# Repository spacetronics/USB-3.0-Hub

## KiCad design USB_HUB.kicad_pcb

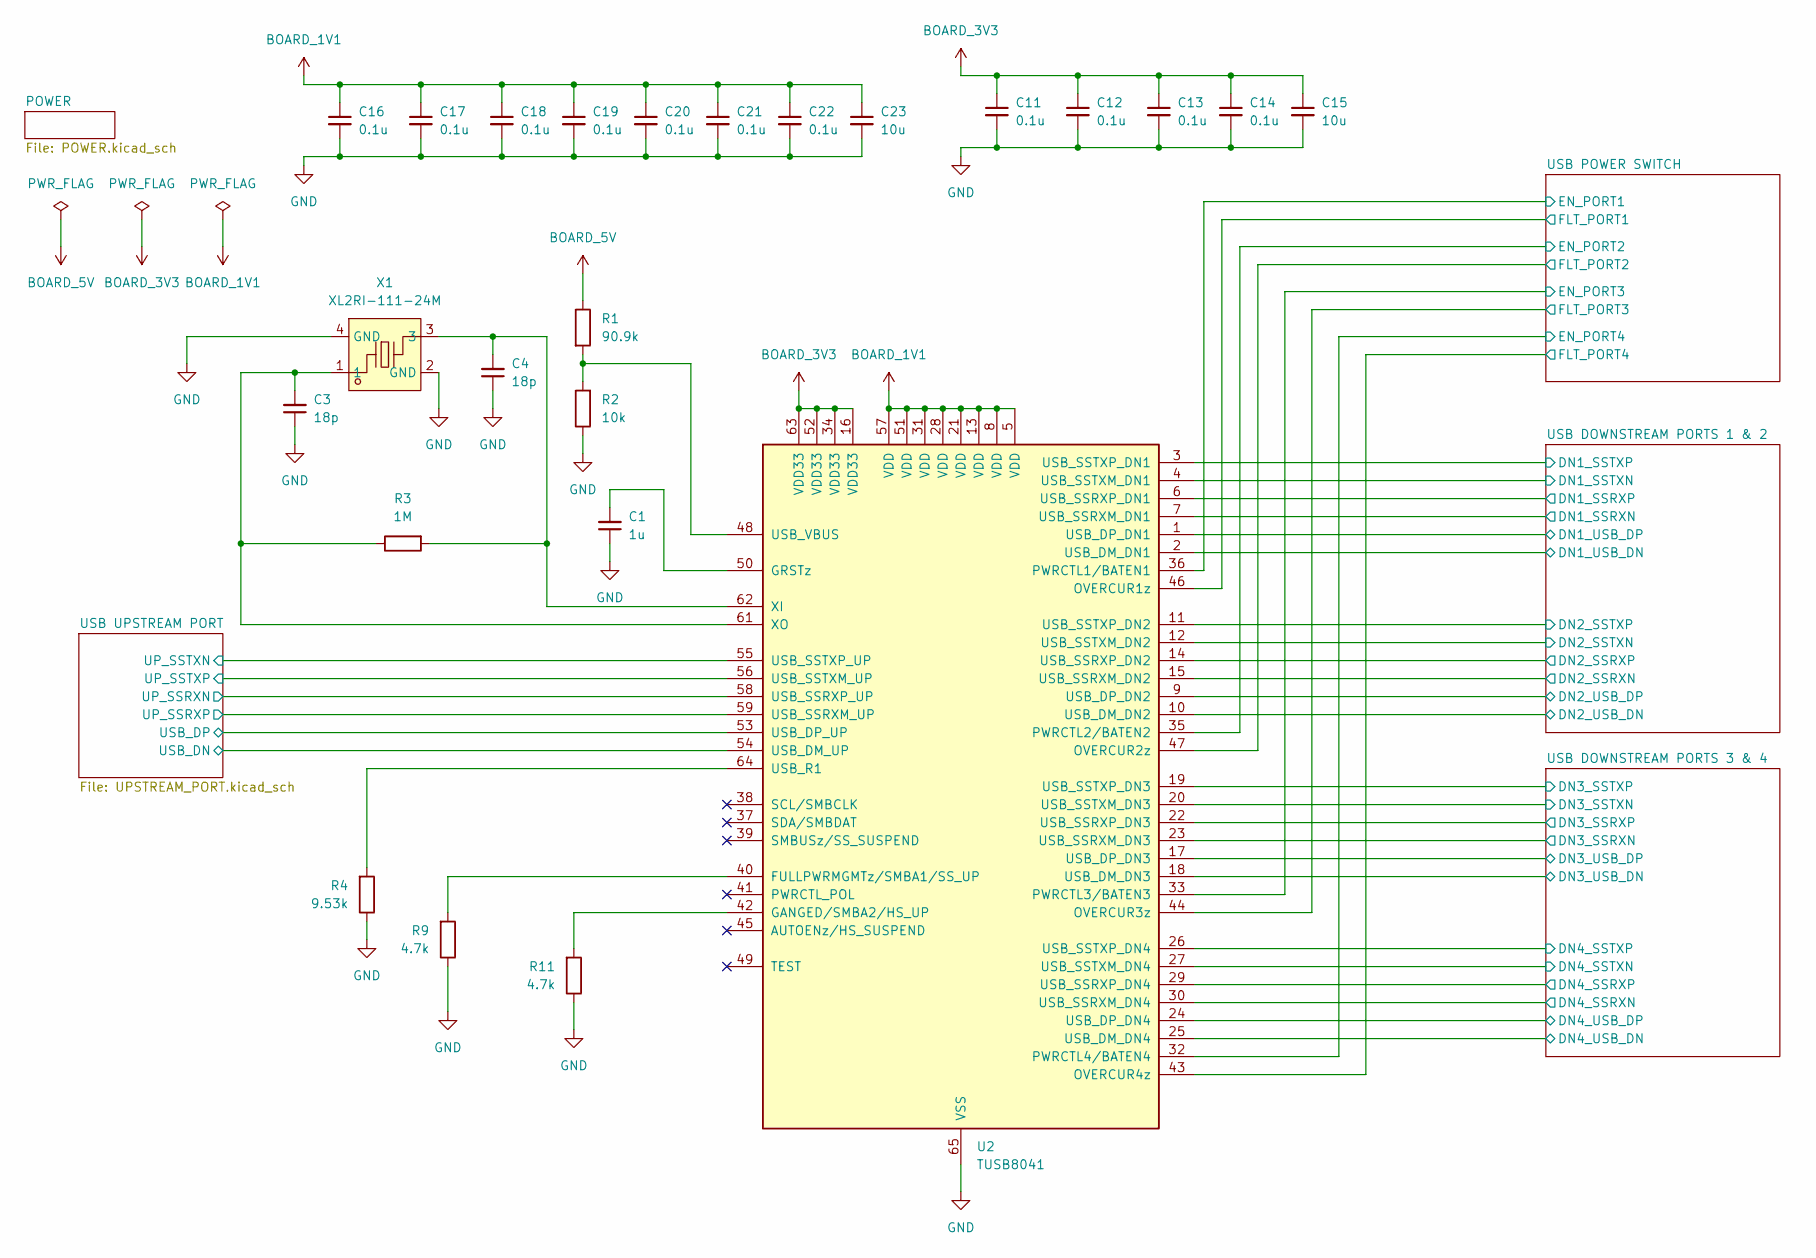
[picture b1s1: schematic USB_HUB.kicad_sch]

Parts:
C1: 1u; C_0402_1005Metric
C3, C4: 18p; C_0402_1005Metric
C11, C12, C13, C14, C16, C17, C18, C19, C20, C21, C22: 0.1u; C_0402_1005Metric
C15, C23: 10u; C_0402_1005Metric
R1: 90.9k; R_0402_1005Metric
R2: 10k; R_0402_1005Metric
R3: 1M; R_0402_1005Metric
R4: 9.53k; R_0402_1005Metric
R9, R11: 4.7k; R_0402_1005Metric
U2: TUSB8041; QFN-64-1EP_9x9mm_P0.5mm_EP6x6mm_ThermalVias
X1: XL2RI-111-24M; CRYSTAL-SMD_4P-L3.2-W2.5-BL; MPN XL2RI-111-24M; LCSC Part C20617586

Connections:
/USB DOWNSTREAM PORTS 1 & 2/DN1_SSRXN: U2.7 (USB_SSRXM_DN1); also elsewhere on the board
/USB DOWNSTREAM PORTS 1 & 2/DN1_SSRXP: U2.6 (USB_SSRXP_DN1); also elsewhere on the board
/USB DOWNSTREAM PORTS 1 & 2/DN1_SSTXN: U2.4 (USB_SSTXM_DN1); also elsewhere on the board
/USB DOWNSTREAM PORTS 1 & 2/DN1_SSTXP: U2.3 (USB_SSTXP_DN1); also elsewhere on the board
/USB DOWNSTREAM PORTS 1 & 2/DN1_USB_DN: U2.2 (USB_DM_DN1); also elsewhere on the board
/USB DOWNSTREAM PORTS 1 & 2/DN1_USB_DP: U2.1 (USB_DP_DN1); also elsewhere on the board
/USB DOWNSTREAM PORTS 1 & 2/DN2_SSRXN: U2.15 (USB_SSRXM_DN2); also elsewhere on the board
/USB DOWNSTREAM PORTS 1 & 2/DN2_SSRXP: U2.14 (USB_SSRXP_DN2); also elsewhere on the board
/USB DOWNSTREAM PORTS 1 & 2/DN2_SSTXN: U2.12 (USB_SSTXM_DN2); also elsewhere on the board
/USB DOWNSTREAM PORTS 1 & 2/DN2_SSTXP: U2.11 (USB_SSTXP_DN2); also elsewhere on the board
/USB DOWNSTREAM PORTS 1 & 2/DN2_USB_DN: U2.10 (USB_DM_DN2); also elsewhere on the board
/USB DOWNSTREAM PORTS 1 & 2/DN2_USB_DP: U2.9 (USB_DP_DN2); also elsewhere on the board
/USB DOWNSTREAM PORTS 3 & 4/DN3_SSRXN: U2.23 (USB_SSRXM_DN3); also elsewhere on the board
/USB DOWNSTREAM PORTS 3 & 4/DN3_SSRXP: U2.22 (USB_SSRXP_DN3); also elsewhere on the board
/USB DOWNSTREAM PORTS 3 & 4/DN3_SSTXN: U2.20 (USB_SSTXM_DN3); also elsewhere on the board
/USB DOWNSTREAM PORTS 3 & 4/DN3_SSTXP: U2.19 (USB_SSTXP_DN3); also elsewhere on the board
/USB DOWNSTREAM PORTS 3 & 4/DN3_USB_DN: U2.18 (USB_DM_DN3); also elsewhere on the board
/USB DOWNSTREAM PORTS 3 & 4/DN3_USB_DP: U2.17 (USB_DP_DN3); also elsewhere on the board
/USB DOWNSTREAM PORTS 3 & 4/DN4_SSRXN: U2.30 (USB_SSRXM_DN4); also elsewhere on the board
/USB DOWNSTREAM PORTS 3 & 4/DN4_SSRXP: U2.29 (USB_SSRXP_DN4); also elsewhere on the board
/USB DOWNSTREAM PORTS 3 & 4/DN4_SSTXN: U2.27 (USB_SSTXM_DN4); also elsewhere on the board
/USB DOWNSTREAM PORTS 3 & 4/DN4_SSTXP: U2.26 (USB_SSTXP_DN4); also elsewhere on the board
/USB DOWNSTREAM PORTS 3 & 4/DN4_USB_DN: U2.25 (USB_DM_DN4); also elsewhere on the board
/USB DOWNSTREAM PORTS 3 & 4/DN4_USB_DP: U2.24 (USB_DP_DN4); also elsewhere on the board
/USB POWER SWITCH/EN_PORT1: U2.36 (PWRCTL1/BATEN1); also elsewhere on the board
/USB POWER SWITCH/EN_PORT2: U2.35 (PWRCTL2/BATEN2); also elsewhere on the board
/USB POWER SWITCH/EN_PORT3: U2.33 (PWRCTL3/BATEN3); also elsewhere on the board
/USB POWER SWITCH/EN_PORT4: U2.32 (PWRCTL4/BATEN4); also elsewhere on the board
/USB POWER SWITCH/FLT_PORT1: U2.46 (OVERCUR1z); also elsewhere on the board
/USB POWER SWITCH/FLT_PORT2: U2.47 (OVERCUR2z); also elsewhere on the board
/USB POWER SWITCH/FLT_PORT3: U2.44 (OVERCUR3z); also elsewhere on the board
/USB POWER SWITCH/FLT_PORT4: U2.43 (OVERCUR4z); also elsewhere on the board
/USB UPSTREAM PORT/UP_SSRXN: U2.58 (USB_SSRXP_UP); also elsewhere on the board
/USB UPSTREAM PORT/UP_SSRXP: U2.59 (USB_SSRXM_UP); also elsewhere on the board
/USB UPSTREAM PORT/UP_SSTXN: U2.55 (USB_SSTXP_UP); also elsewhere on the board
/USB UPSTREAM PORT/UP_SSTXP: U2.56 (USB_SSTXM_UP); also elsewhere on the board
/USB UPSTREAM PORT/USB_DN: U2.54 (USB_DM_UP); also elsewhere on the board
/USB UPSTREAM PORT/USB_DP: U2.53 (USB_DP_UP); also elsewhere on the board
BOARD_1V1: C16.1, C17.1, C18.1, C19.1, C20.1, C21.1, C22.1, C23.1, U2.5 (VDD), U2.8 (VDD), U2.13 (VDD), U2.21 (VDD), U2.28 (VDD), U2.31 (VDD), U2.51 (VDD), U2.57 (VDD); also elsewhere on the board
BOARD_3V3: C11.1, C12.1, C13.1, C14.1, C15.1, U2.16 (VDD33), U2.34 (VDD33), U2.52 (VDD33), U2.63 (VDD33); also elsewhere on the board
BOARD_5V: R1.1; also elsewhere on the board
GND: C1.1, C3.1, C4.1, C11.2, C12.2, C13.2, C14.2, C15.2, C16.2, C17.2, C18.2, C19.2, C20.2, C21.2, C22.2, C23.2, R2.1, R4.1, R9.1, R11.1, U2.65 (VSS), X1.2 (GND), X1.4 (GND); also elsewhere on the board
unnamed: R9.2, U2.40 (FULLPWRMGMTz/SMBA1/SS_UP)
unnamed: R11.2, U2.42 (GANGED/SMBA2/HS_UP)
unnamed: C1.2, U2.50 (GRSTz)
unnamed: R4.2, U2.64 (USB_R1)
unnamed: R1.2, R2.2, U2.48 (USB_VBUS)
unnamed: C4.2, R3.2, U2.62 (XI), X1.3
unnamed: C3.2, R3.1, U2.61 (XO), X1.1

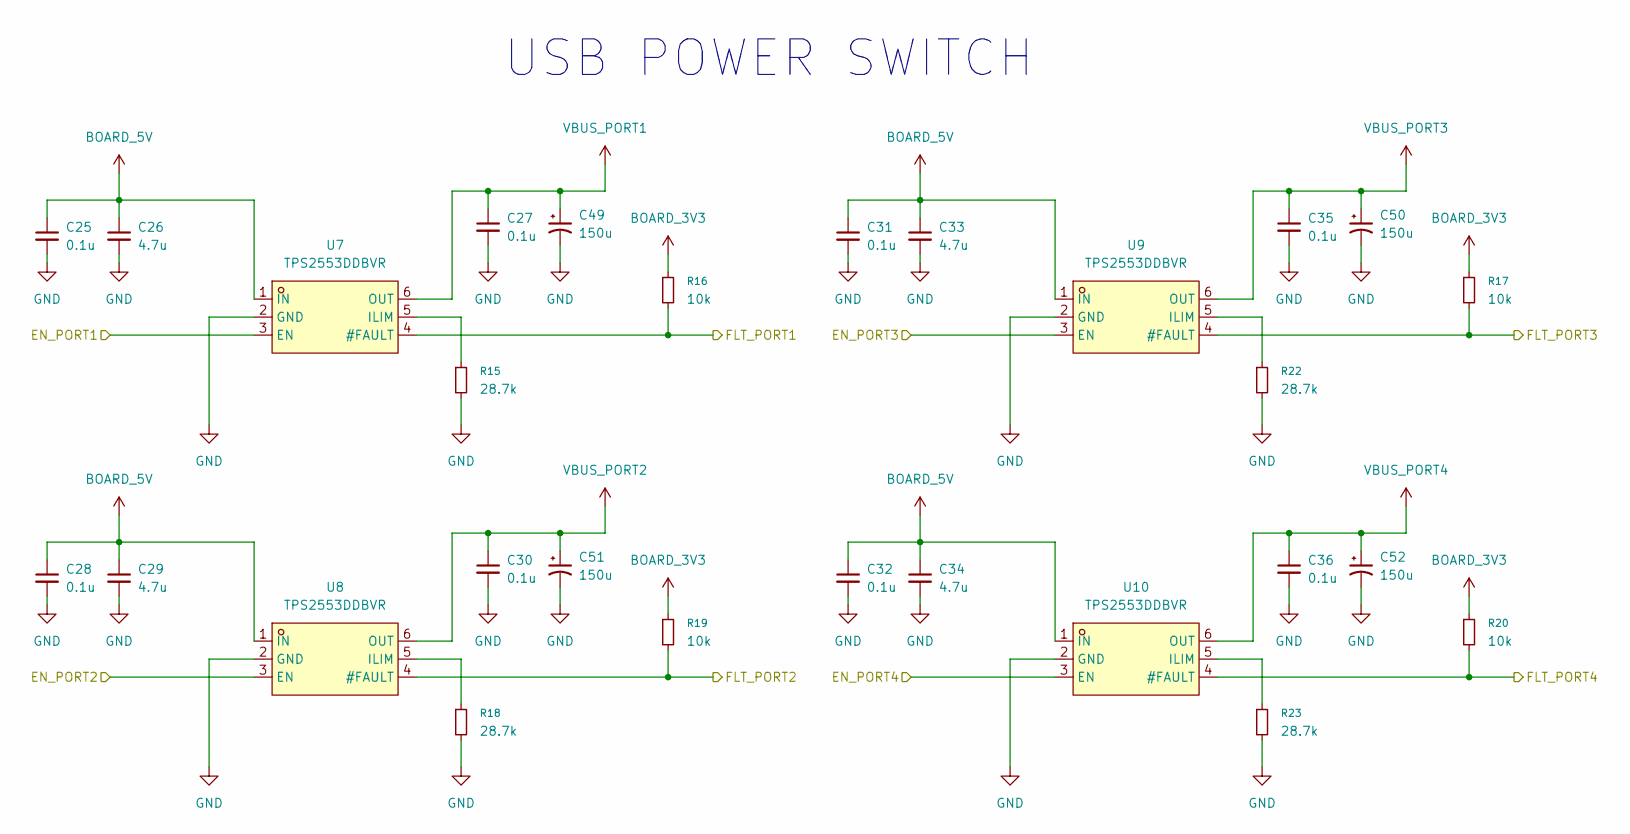
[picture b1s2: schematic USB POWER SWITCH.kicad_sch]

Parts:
C25, C27, C28, C30, C31, C32, C35, C36: 0.1u; C_0402_1005Metric
C26, C29, C33, C34: 4.7u; C_0402_1005Metric
C49, C50, C51, C52: 150u; CP_EIA-3528-15_AVX-H_HandSolder
R15, R18, R22, R23: 28.7k; R_0402_1005Metric
R16, R17, R19, R20: 10k; R_0402_1005Metric
U7, U8, U9, U10: TPS2553DDBVR; SOT-23-6_L2.9-W1.6-P0.95-LS2.8-BL; MPN TPS2553DDBVR; LCSC Part C521201

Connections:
/USB POWER SWITCH/EN_PORT1: U7.3 (EN); also elsewhere on the board
/USB POWER SWITCH/EN_PORT2: U8.3 (EN); also elsewhere on the board
/USB POWER SWITCH/EN_PORT3: U9.3 (EN); also elsewhere on the board
/USB POWER SWITCH/EN_PORT4: U10.3 (EN); also elsewhere on the board
/USB POWER SWITCH/FLT_PORT1: R16.2, U7.4 (#FAULT); also elsewhere on the board
/USB POWER SWITCH/FLT_PORT2: R19.2, U8.4 (#FAULT); also elsewhere on the board
/USB POWER SWITCH/FLT_PORT3: R17.2, U9.4 (#FAULT); also elsewhere on the board
/USB POWER SWITCH/FLT_PORT4: R20.2, U10.4 (#FAULT); also elsewhere on the board
BOARD_3V3: R16.1, R17.1, R19.1, R20.1; also elsewhere on the board
BOARD_5V: C25.1, C26.1, C28.1, C29.1, C31.1, C32.1, C33.1, C34.1, U7.1 (IN), U8.1 (IN), U9.1 (IN), U10.1 (IN); also elsewhere on the board
GND: C25.2, C26.2, C27.2, C28.2, C29.2, C30.2, C31.2, C32.2, C33.2, C34.2, C35.2, C36.2, C49.2, C50.2, C51.2, C52.2, R15.2, R18.2, R22.2, R23.2, U7.2 (GND), U8.2 (GND), U9.2 (GND), U10.2 (GND); also elsewhere on the board
unnamed: R15.1, U7.5 (ILIM)
unnamed: R18.1, U8.5 (ILIM)
unnamed: R22.1, U9.5 (ILIM)
unnamed: R23.1, U10.5 (ILIM)
VBUS_PORT1: C27.1, C49.1, U7.6 (OUT); also elsewhere on the board
VBUS_PORT2: C30.1, C51.1, U8.6 (OUT); also elsewhere on the board
VBUS_PORT3: C35.1, C50.1, U9.6 (OUT); also elsewhere on the board
VBUS_PORT4: C36.1, C52.1, U10.6 (OUT); also elsewhere on the board

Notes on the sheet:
USB POWER SWITCH

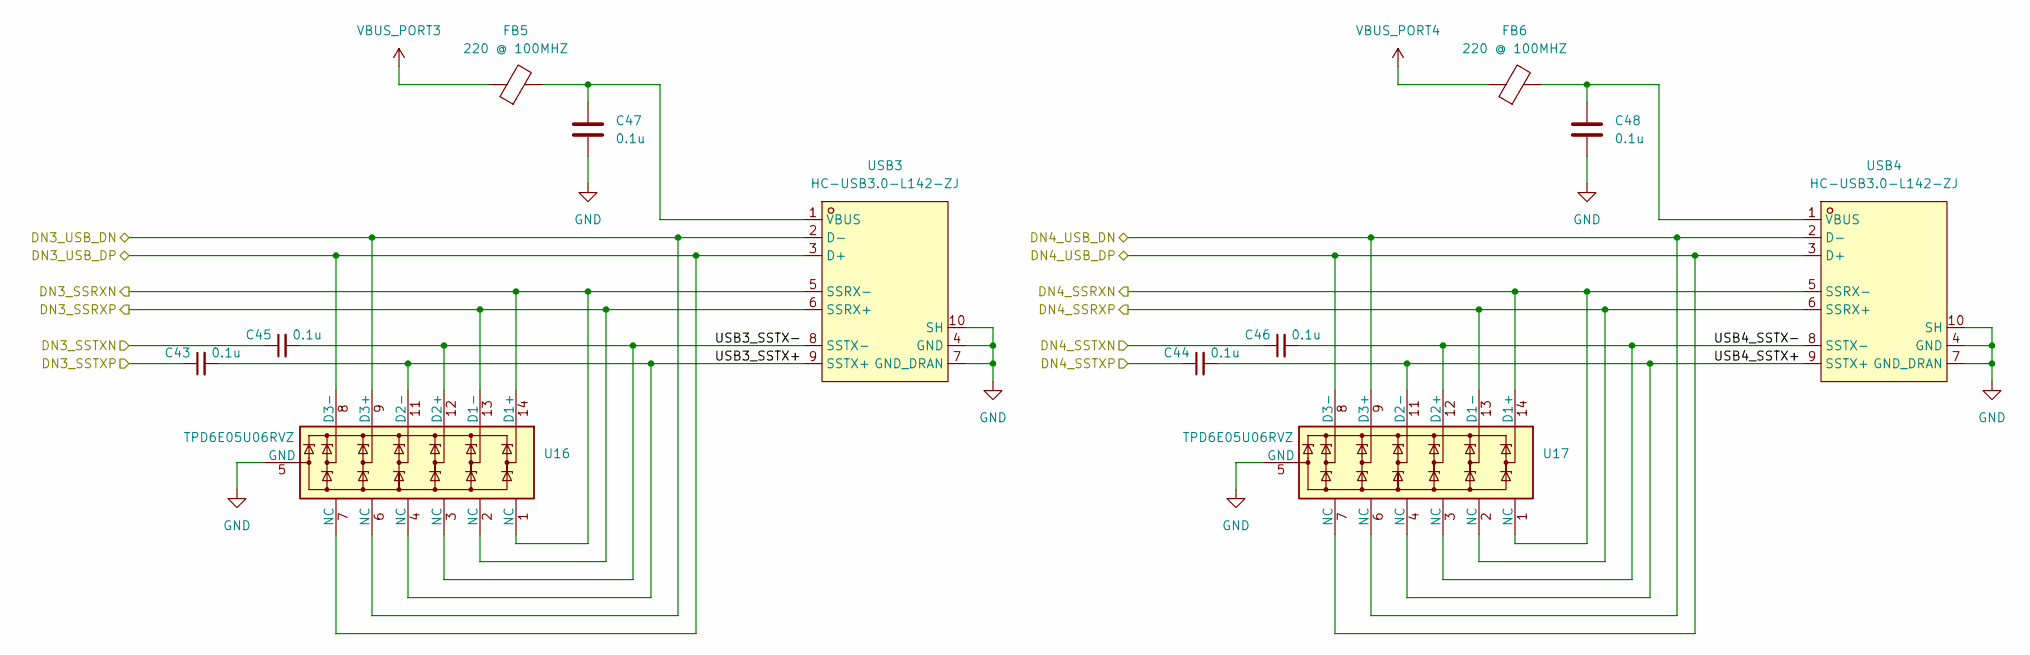
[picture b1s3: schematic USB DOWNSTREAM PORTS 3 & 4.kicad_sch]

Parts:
C43, C44, C45, C46: 0.1u; C_0201_0603Metric
C47, C48: 0.1u; C_0402_1005Metric
FB5, FB6: 220 @ 100MHZ; L_0603_1608Metric
U16, U17: TPD6E05U06RVZ; Texas_R-PUSON-N14
USB3, USB4: HC-USB3.0-L142-ZJ; USB-C-SMD_HC-USB3.0-L142-ZJ; MPN HC-USB3.0-L142-ZJ; LCSC Part C7501879

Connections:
/USB DOWNSTREAM PORTS 3 & 4/DN3_SSRXN: U16.1 (NC), U16.14 (D1+), USB3.5 (SSRX-); also elsewhere on the board
/USB DOWNSTREAM PORTS 3 & 4/DN3_SSRXP: U16.2 (NC), U16.13 (D1-), USB3.6 (SSRX+); also elsewhere on the board
/USB DOWNSTREAM PORTS 3 & 4/DN3_SSTXN: C45.1; also elsewhere on the board
/USB DOWNSTREAM PORTS 3 & 4/DN3_SSTXP: C43.1; also elsewhere on the board
/USB DOWNSTREAM PORTS 3 & 4/DN3_USB_DN: U16.6 (NC), U16.9 (D3+), USB3.2 (D-); also elsewhere on the board
/USB DOWNSTREAM PORTS 3 & 4/DN3_USB_DP: U16.7 (NC), U16.8 (D3-), USB3.3 (D+); also elsewhere on the board
/USB DOWNSTREAM PORTS 3 & 4/DN4_SSRXN: U17.1 (NC), U17.14 (D1+), USB4.5 (SSRX-); also elsewhere on the board
/USB DOWNSTREAM PORTS 3 & 4/DN4_SSRXP: U17.2 (NC), U17.13 (D1-), USB4.6 (SSRX+); also elsewhere on the board
/USB DOWNSTREAM PORTS 3 & 4/DN4_SSTXN: C46.1; also elsewhere on the board
/USB DOWNSTREAM PORTS 3 & 4/DN4_SSTXP: C44.1; also elsewhere on the board
/USB DOWNSTREAM PORTS 3 & 4/DN4_USB_DN: U17.6 (NC), U17.9 (D3+), USB4.2 (D-); also elsewhere on the board
/USB DOWNSTREAM PORTS 3 & 4/DN4_USB_DP: U17.7 (NC), U17.8 (D3-), USB4.3 (D+); also elsewhere on the board
/USB DOWNSTREAM PORTS 3 & 4/USB3_SSTX+: C43.2, U16.4 (NC), U16.11 (D2-), USB3.9 (SSTX+)
/USB DOWNSTREAM PORTS 3 & 4/USB3_SSTX-: C45.2, U16.3 (NC), U16.12 (D2+), USB3.8 (SSTX-)
/USB DOWNSTREAM PORTS 3 & 4/USB4_SSTX+: C44.2, U17.4 (NC), U17.11 (D2-), USB4.9 (SSTX+)
/USB DOWNSTREAM PORTS 3 & 4/USB4_SSTX-: C46.2, U17.3 (NC), U17.12 (D2+), USB4.8 (SSTX-)
GND: C47.2, C48.2, U16.5 (GND), U16.10 (GND), U17.5 (GND), U17.10 (GND), USB3.4 (GND), USB3.7 (GND_DRAN), USB3.10 (SH), USB4.4 (GND), USB4.7 (GND_DRAN), USB4.10 (SH); also elsewhere on the board
unnamed: C47.1, FB5.2, USB3.1 (VBUS)
unnamed: C48.1, FB6.2, USB4.1 (VBUS)
VBUS_PORT3: FB5.1; also elsewhere on the board
VBUS_PORT4: FB6.1; also elsewhere on the board

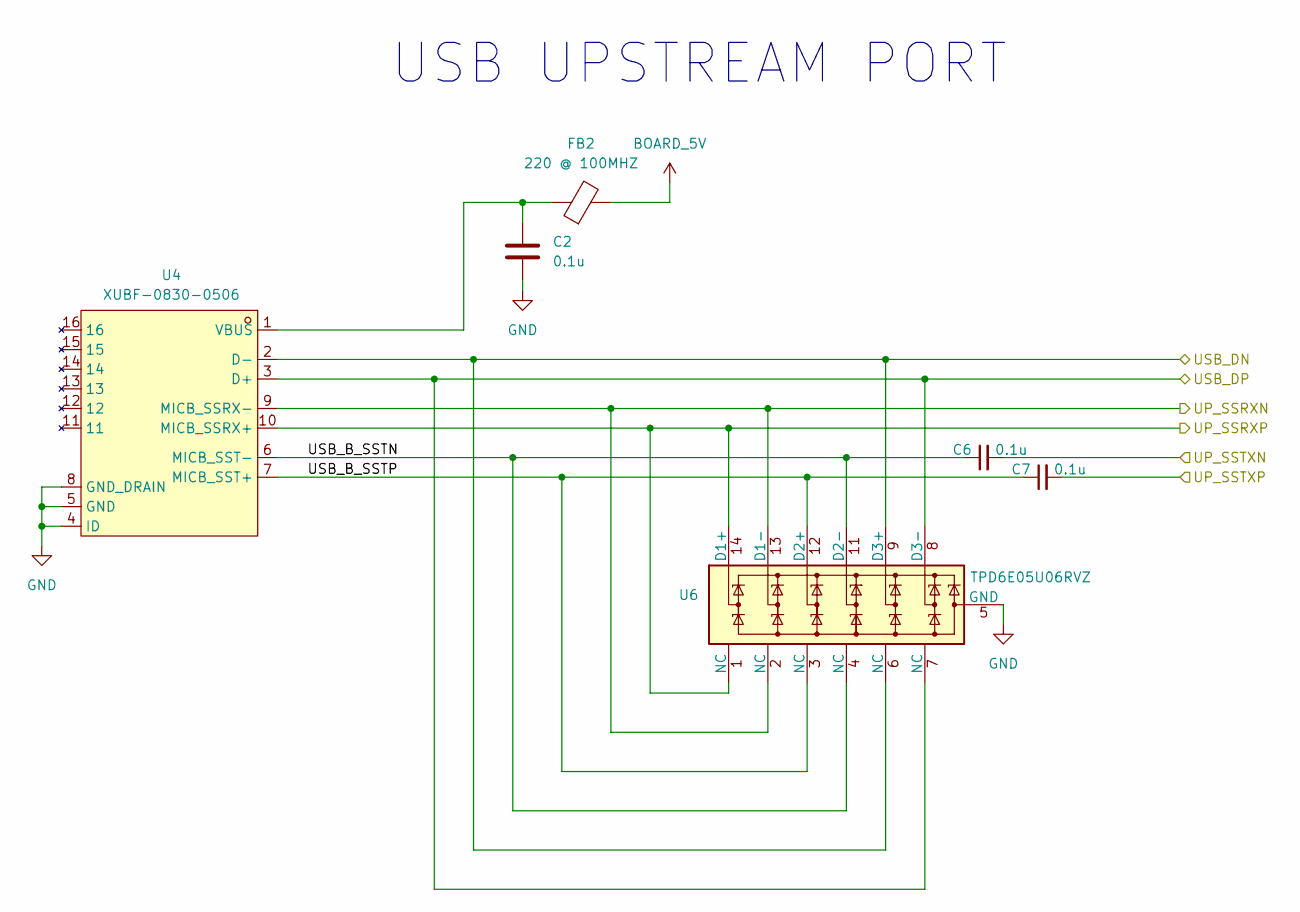
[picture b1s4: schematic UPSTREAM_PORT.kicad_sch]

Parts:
C2: 0.1u; C_0402_1005Metric
C6, C7: 0.1u; C_0201_0603Metric
FB2: 220 @ 100MHZ; L_0603_1608Metric
U4: XUBF-0830-0506; CONN-SMD_XUBF-0830-0506; MPN XUBF-0830-0506; LCSC Part C18202148
U6: TPD6E05U06RVZ; Texas_R-PUSON-N14

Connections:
/USB UPSTREAM PORT/UP_SSRXN: U4.9 (MICB_SSRX-), U6.2 (NC), U6.13 (D1-); also elsewhere on the board
/USB UPSTREAM PORT/UP_SSRXP: U4.10 (MICB_SSRX+), U6.1 (NC), U6.14 (D1+); also elsewhere on the board
/USB UPSTREAM PORT/UP_SSTXN: C6.2; also elsewhere on the board
/USB UPSTREAM PORT/UP_SSTXP: C7.2; also elsewhere on the board
/USB UPSTREAM PORT/USB_B_SSTN: C6.1, U4.6 (MICB_SST-), U6.4 (NC), U6.11 (D2-)
/USB UPSTREAM PORT/USB_B_SSTP: C7.1, U4.7 (MICB_SST+), U6.3 (NC), U6.12 (D2+)
/USB UPSTREAM PORT/USB_DN: U4.2 (D-), U6.6 (NC), U6.9 (D3+); also elsewhere on the board
/USB UPSTREAM PORT/USB_DP: U4.3 (D+), U6.7 (NC), U6.8 (D3-); also elsewhere on the board
BOARD_5V: FB2.2; also elsewhere on the board
GND: C2.2, U4.4 (ID), U4.5 (GND), U4.8 (GND_DRAIN), U6.5 (GND), U6.10 (GND); also elsewhere on the board
unnamed: C2.1, FB2.1, U4.1 (VBUS)

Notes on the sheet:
USB UPSTREAM PORT

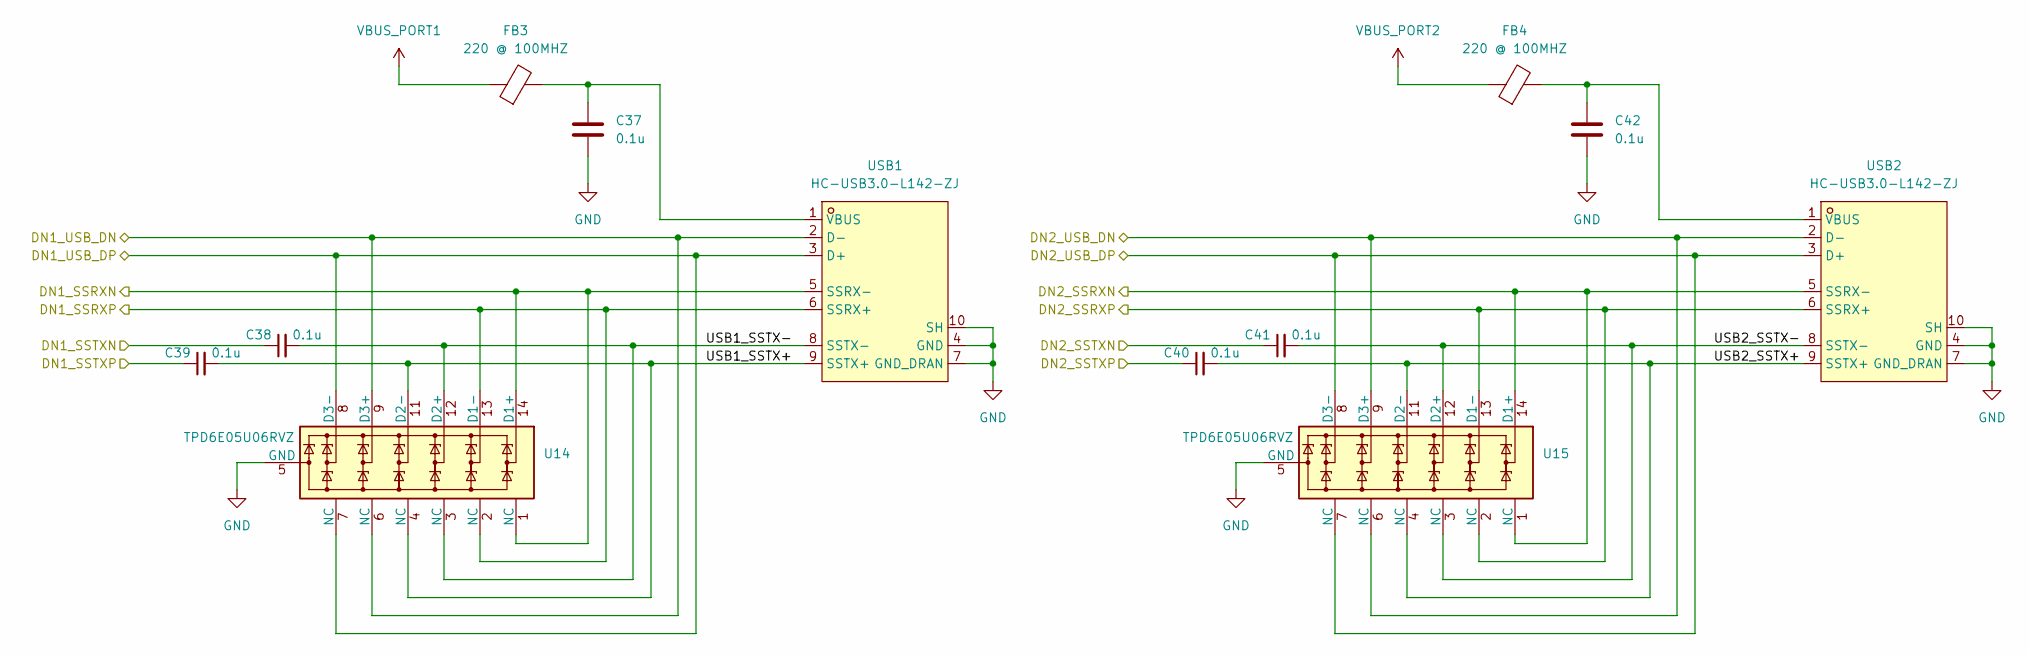
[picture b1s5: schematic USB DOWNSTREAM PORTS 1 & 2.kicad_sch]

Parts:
C37, C42: 0.1u; C_0402_1005Metric
C38, C39, C40, C41: 0.1u; C_0201_0603Metric
FB3, FB4: 220 @ 100MHZ; L_0603_1608Metric
U14, U15: TPD6E05U06RVZ; Texas_R-PUSON-N14
USB1, USB2: HC-USB3.0-L142-ZJ; USB-C-SMD_HC-USB3.0-L142-ZJ; MPN HC-USB3.0-L142-ZJ; LCSC Part C7501879

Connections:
/USB DOWNSTREAM PORTS 1 & 2/DN1_SSRXN: U14.1 (NC), U14.14 (D1+), USB1.5 (SSRX-); also elsewhere on the board
/USB DOWNSTREAM PORTS 1 & 2/DN1_SSRXP: U14.2 (NC), U14.13 (D1-), USB1.6 (SSRX+); also elsewhere on the board
/USB DOWNSTREAM PORTS 1 & 2/DN1_SSTXN: C38.1; also elsewhere on the board
/USB DOWNSTREAM PORTS 1 & 2/DN1_SSTXP: C39.1; also elsewhere on the board
/USB DOWNSTREAM PORTS 1 & 2/DN1_USB_DN: U14.6 (NC), U14.9 (D3+), USB1.2 (D-); also elsewhere on the board
/USB DOWNSTREAM PORTS 1 & 2/DN1_USB_DP: U14.7 (NC), U14.8 (D3-), USB1.3 (D+); also elsewhere on the board
/USB DOWNSTREAM PORTS 1 & 2/DN2_SSRXN: U15.1 (NC), U15.14 (D1+), USB2.5 (SSRX-); also elsewhere on the board
/USB DOWNSTREAM PORTS 1 & 2/DN2_SSRXP: U15.2 (NC), U15.13 (D1-), USB2.6 (SSRX+); also elsewhere on the board
/USB DOWNSTREAM PORTS 1 & 2/DN2_SSTXN: C41.1; also elsewhere on the board
/USB DOWNSTREAM PORTS 1 & 2/DN2_SSTXP: C40.1; also elsewhere on the board
/USB DOWNSTREAM PORTS 1 & 2/DN2_USB_DN: U15.6 (NC), U15.9 (D3+), USB2.2 (D-); also elsewhere on the board
/USB DOWNSTREAM PORTS 1 & 2/DN2_USB_DP: U15.7 (NC), U15.8 (D3-), USB2.3 (D+); also elsewhere on the board
/USB DOWNSTREAM PORTS 1 & 2/USB1_SSTX+: C39.2, U14.4 (NC), U14.11 (D2-), USB1.9 (SSTX+)
/USB DOWNSTREAM PORTS 1 & 2/USB1_SSTX-: C38.2, U14.3 (NC), U14.12 (D2+), USB1.8 (SSTX-)
/USB DOWNSTREAM PORTS 1 & 2/USB2_SSTX+: C40.2, U15.4 (NC), U15.11 (D2-), USB2.9 (SSTX+)
/USB DOWNSTREAM PORTS 1 & 2/USB2_SSTX-: C41.2, U15.3 (NC), U15.12 (D2+), USB2.8 (SSTX-)
GND: C37.2, C42.2, U14.5 (GND), U14.10 (GND), U15.5 (GND), U15.10 (GND), USB1.4 (GND), USB1.7 (GND_DRAN), USB1.10 (SH), USB2.4 (GND), USB2.7 (GND_DRAN), USB2.10 (SH); also elsewhere on the board
unnamed: C37.1, FB3.2, USB1.1 (VBUS)
unnamed: C42.1, FB4.2, USB2.1 (VBUS)
VBUS_PORT1: FB3.1; also elsewhere on the board
VBUS_PORT2: FB4.1; also elsewhere on the board

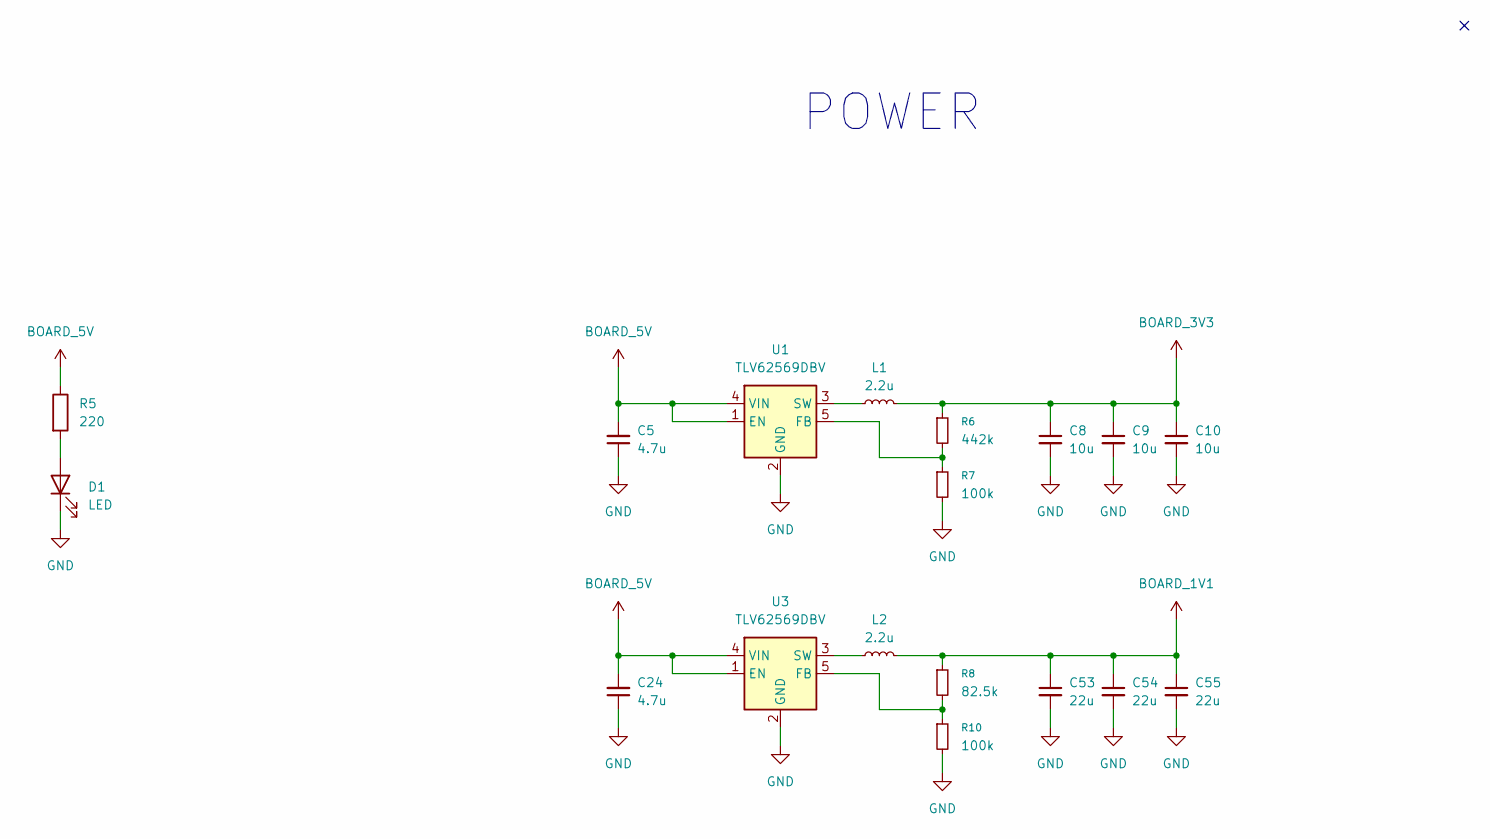
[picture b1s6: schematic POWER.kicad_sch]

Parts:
C5, C24: 4.7u; C_0805_2012Metric
C8, C9, C10: 10u; C_0402_1005Metric
C53, C54, C55: 22u; C_0402_1005Metric
D1: LED; LED_0603_1608Metric_Pad1.05x0.95mm_HandSolder
L1, L2: 2.2u; L_APV_APH0630
R5: 220; R_0402_1005Metric_Pad0.72x0.64mm_HandSolder
R6: 442k; R_0402_1005Metric
R7, R10: 100k; R_0402_1005Metric
R8: 82.5k; R_0402_1005Metric
U1, U3: TLV62569DBV; SOT-23-5

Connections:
BOARD_1V1: C53.1, C54.1, C55.1, L2.2, R8.1; also elsewhere on the board
BOARD_3V3: C8.1, C9.1, C10.1, L1.2, R6.1; also elsewhere on the board
BOARD_5V: C5.2, C24.2, R5.1, U1.1 (EN), U1.4 (VIN), U3.1 (EN), U3.4 (VIN); also elsewhere on the board
GND: C5.1, C8.2, C9.2, C10.2, C24.1, C53.2, C54.2, C55.2, D1.1 (K), R7.2, R10.2, U1.2 (GND), U3.2 (GND); also elsewhere on the board
unnamed: D1.2 (A), R5.2
unnamed: R6.2, R7.1, U1.5 (FB)
unnamed: L1.1, U1.3 (SW)
unnamed: R8.2, R10.1, U3.5 (FB)
unnamed: L2.1, U3.3 (SW)

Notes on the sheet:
POWER

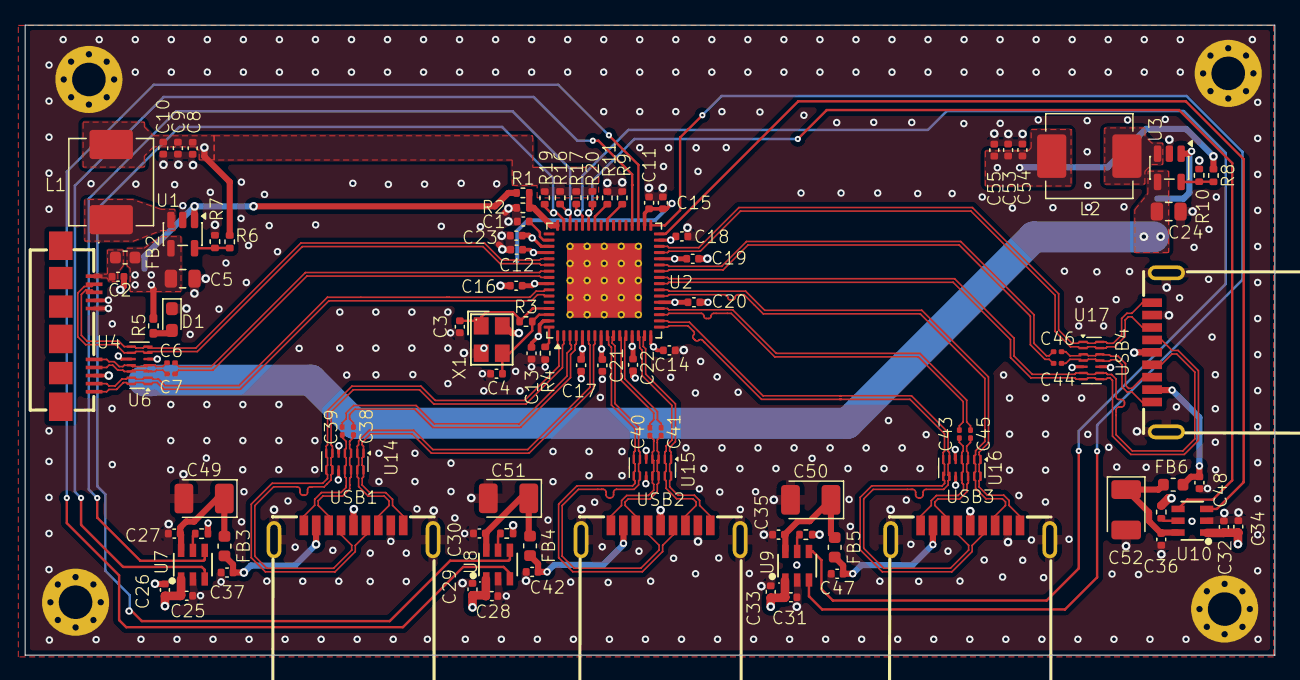
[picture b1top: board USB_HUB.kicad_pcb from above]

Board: 4 copper layers, 100.6 x 50.7 mm, 100 parts (0 on the bottom side), 77 nets.
